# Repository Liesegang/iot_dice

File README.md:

# IoT Dice

サイコロの姿勢・IMUデータをBluetooth Low Energyでブラウザに送り、3D表示するプロジェクトです。

| バージョン | MCU | IMU |
| --- | --- | --- |
| [v1](v1/README.md) | nRF5340 | BNO085 |
| [v2](v2/README.md) | nRF54L15 / ES4L15BA1 | LSM6DSV320X |

```text
v1/
  firmware/  nRF5340用
  hardware/  旧基板データ・回路図
  software/  v1 Webアプリ
v2/
  firmware/  nRF54L15用
  hardware/  Dice 2a基板データ・回路図
  software/  v2 Webアプリ
```

v2では電源投入後にLED2が点滅し、BLE接続中にLED1が点灯します。LSM6DSV320XはLow-gを±16g・120 Hz、High-gを±320g・960 Hz、角速度を±4000dpsに設定しています。High-gはFIFOから取得し、通知間の衝突ピークを保持します。BLE通知は通常約60 Hz、予測／軌跡モードは最大120 Hzです。Web画面では角速度・Low-g・High-g・重力除去後の加速度を4グラフで表示します。

WebアプリはChromeまたはEdgeのHTTPS / localhostで使えます。

```sh
cd v2/software
npm ci
npm run dev -- --host localhost
```

表示されたURLを開き、「サイコロを接続」から`dice`を選んでください。同名デバイスが複数ある場合は対象基板のアドレスで識別します。

GitHub Pagesのワークフローはv1・v2を両方ビルドし、次回デプロイ時にはルートと`/v2/`でv2、`/v1/`でv1を公開します。ファームウェアのビルド・書き込み手順と配線は各バージョンのREADMEを参照してください。

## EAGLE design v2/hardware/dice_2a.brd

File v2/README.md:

# IoT Dice v2 / Dice 2a

KAGA FEI ES4L15BA1（nRF54L15）とLSM6DSV320Xを使う基板です。部品はCADの`PARTS=LSM6DSV320XTR`と実機の`WHO_AM_I=0x73`で識別しています。IC1のdeviceset名はLSM6DSV16XTRのままなので、ドライバー選択には使いません。

## 動作

- LED2（P1.00）：起動直後から500 msごとにON/OFF。IMU初期化が失敗しても点滅します。
- LED1（P1.01）：BLE接続中に点灯、切断時に消灯。
- IMU設定：Low-gは±16g・120 Hz、High-gは±320g・960 Hz、角速度は±4000dps・120 Hz。通常は約60 Hz、軌跡／予測モードは最大120 HzでBLE通知。
- 通常モード：姿勢・角速度・重力除去後の加速度・Low-g／High-g生値と通知間のHigh-gピークを送信。
- 予測モード：最初の衝突前の状態と時刻・投擲番号を送信し、Webで15 mmのサイコロの出目を予測します。実機記録を使う強化学習と検証・テスト評価を追加しました。現時点では必要数の学習用記録が揃っておらず、モデルは未学習・精度未検証です。

SFLPのGame Rotationは磁気センサーを使わないため、ヨーの絶対方位は任意でドリフトすることがあります。

## 配線

| 用途 | nRF54L15 GPIO | モジュールパッド |
| --- | --- | --- |
| LED1 / BLE | P1.01 | 3 |
| LED2 / 起動 | P1.00 | 4 |
| IMU SCK | P2.04 | 9 |
| IMU MOSI | P0.03 | 8 |
| IMU MISO | P0.04 | 7 |
| IMU CS | P2.01 | 10 |
| IMU INT1（未使用） | P1.03 | 5 |

SPIはZephyrのGPIO bitbang、mode 3、設定上限500 kHzです。SCKとデータ線がP2/P0に分かれているため、この配線のまま単一のハードウェアSPIMでは駆動できません。実際の速度はGPIO操作の処理時間にも依存します。FIFOをポーリングします。

P1.00/P1.01をLEDに使うため、低周波クロックは校正ありの内部RCを使用します。電源は安定化された3.3Vを使用してください。

| CON1ピン | 信号 |
| --- | --- |
| 1 | NRST |
| 2 | +3V3 |
| 3 | SWDIO |
| 4 | GND |
| 5 | SWCLK |
| 6 | 未接続 |

基板・回路図は[hardware](hardware/)にあります。`.fbrd` / `.fsch`は元のFusionファイル、`.brd` / `.sch`は取り出したEagle XMLです。

## ビルド・書き込み

nRF Connect SDK 3.4.0の環境で、リポジトリのルートから実行します。

```sh
west build -b nrf54l15dk/nrf54l15/cpuapp -d v2/firmware/build v2/firmware
```

SDKのDKターゲットに`app.overlay`で実基板の配線を適用します。v1用HEXやネットワークコア用ファームウェアはこの基板へ書き込まないでください。

J-Linkとnrfutil deviceを使う場合は対象シリアル番号を確認してから書き込みます。

```sh
nrfutil device list
nrfutil device program \
  --firmware v2/firmware/build/firmware/zephyr/zephyr.hex \
  --serial-number <J-Linkのシリアル番号> \
  --family nrf54l --swd-clock-frequency 1000 \
  --options chip_erase_mode=ERASE_RANGES_TOUCHED_BY_FIRMWARE,verify=VERIFY_READ,reset=RESET_DEFAULT
```

全消去を使わず、HEXに含まれるコード領域だけを書き込みます。RTTログとELFの`app_debug`シンボルで診断できます。SWDで`app_debug`を読む際、MCUを停止させる必要はありません。

## 姿勢デコードとBLE

LSM6DSV320XのSFLP FIFOは姿勢1件を`[0x0000, X, Y]`、`[0x0001, Z, W]`の2レコードで出力します。X/Y/Z/Wは符号付きbinary16です。2件が揃ってから4成分を正規化し、Wの符号も使います。[STの公式FIFO例](https://github.com/STMicroelectronics/STMems_Standard_C_drivers/blob/master/lsm6dsv320x_STdC/examples/lsm6dsv320x_read_fifo.c)を参照してください。

BLE名は`dice`、サービスUUIDは`d1ce0001-1234-5678-abcd-1234567890ab`。通知UUIDは先頭部分が`d1ce0002`、操作UUIDは`d1ce0003`です。

v3の姿勢／ストリーム通知は100バイトです。従来の58バイトの先頭に続き、Low-g生値、High-g最新値、通知間のHigh-g最大ベクトル、有効性・飽和フラグを含みます。通常モードの速度は0です。衝突通知は76バイト、静止通知は44バイトで、High-gの衝突ピークや最大値を記録します。多バイト値はlittle-endianです。詳細は[ble_orient.hpp](firmware/src/ble_orient.hpp)。Webアプリは従来の22/46/58バイト姿勢、50/58バイト衝突、32/36バイト静止も読めます。High-gが届いていない場合は「未受信」と表示します。

## Webアプリとテスト

```sh
cd v2/software
npm ci
npm run dev -- --host localhost
```

配布用ビルドは`npm run build`、型チェックは`npx tsc --noEmit`、BLE・物理モデル・強化学習の回帰テストは`npm test`です。

投擲の記録、6面校正、学習、モデルの保存と再学習については[software/LEARNING.md](software/LEARNING.md)を参照してください。

姿勢FIFOの回帰テストはSDKのSTドライバーをホスト向けにリンクして実行します。左右の符号、180度を超えた回転、2レコードの組み立て、欠損・不正データからの復帰を検証します。

```sh
STMEMSC_DRIVER_DIR=/opt/nordic/ncs/v3.4.0/modules/hal/st/sensor/stmemsc/lsm6dsv320x_STdC/driver \
  sh v2/firmware/tests/run.sh
```

### 推定軌跡の表示

Web画面の「軌跡 ON」で、静止位置を原点にした相対移動を水色の線で表示します。黄色の点が原点です。X/YはIMUの水平軸（向きは任意）、Zは上向きで、移動量はcm表示です。軌跡の取得に面校正や出目予測のONは不要です。静止を検出すると線を消し、次に動き始めると原点を更新します。センサーの微小な揺れや残留速度では線を生成しません。「軌跡を消す」で手動リセットできます。

位置はファームウェアの推定速度をデバイス時刻で積分した値です。外部の位置計測ではなく、IMU誤差の影響を受けます。8秒までの短い動きを対象とし、250msを超える受信の空白では線を消して積分を止め、次の静止を待ちます。軌跡ON中は予測OFFでも速度付きの通知モードを使いますが、学習記録は予測ONの場合だけ保存します。

### 校正表示・IMUグラフ・学習状態

6面の校正は出目判定と3D描画の両方に反映します。表示はサイコロからIMUへの取付回転を掛け、逆の番号配置では面1と6の材質を交換します。静止が300ms以上続いている場合のみ校正でき、不正な面の組み合わせは採用しません。左上に実機の推定上面を表示します。

右上のIMU波形は直近10秒のX/Y/Z角速度（rad/s）、Low-g生加速度（g）、通知間のHigh-gピーク（g）、重力除去後の加速度（m/s²）の4図です。通信が途切れた部分は線をつなぎません。これらはIMU座標系の値です。

学習の実行状況は左上と学習パネルで確認できます。パネルには学習可能な記録数、不足数、校正前・ジャイロ飽和で除外された確認済み記録数、最終実行時刻とモデル採用結果を表示します。正解未確認の記録は学習されません。過去の記録は「未確認の記録に正解を付ける」から、実際の出目を覚えているものだけ確認できます。

### High-gでの衝突取得

Low-gは±16g・120Hz設定で姿勢・静止判定・速度の推定に使います。High-gは±320g・960Hz設定でFIFOへ保存し、通知間の全サンプルから最大ノルムの符号付きベクトルを残します。低速のBLE通知でも、サンプル済みの短い衝突ピークが表示されます。IMUのサンプル間に収まる衝撃まで保証するものではありません。

現在の実機では、MCUの時刻に基づく姿勢取得は約111 Hz、High-g取得は約887 Hzで、High-gは姿勢の約8倍でした。120／960 Hzは設定値で、これらの実測値やBLE通知速度とは異なります。

High-gの重力除去後のピークを初回衝突判定へ反映し、着地結果には投擲中の最大High-gと飽和判定回数を保存します。姿勢予測の入力は従来どおり初回衝突前の姿勢・角速度・速度で、衝突ピークを予測入力に混ぜません。High-gのピーク時刻はFIFOから取り出した際のMCUのuptimeです。厳密なセンサー採取時刻ではありません。

ジャイロは±4000dpsへ拡大し、換算と飽和閾値を合わせています。過去の±2000dps時の飽和記録は元の情報を維持します。高gのゼロ点精度はLow-gより低いため、小さい動きと静止にはLow-gを使います。

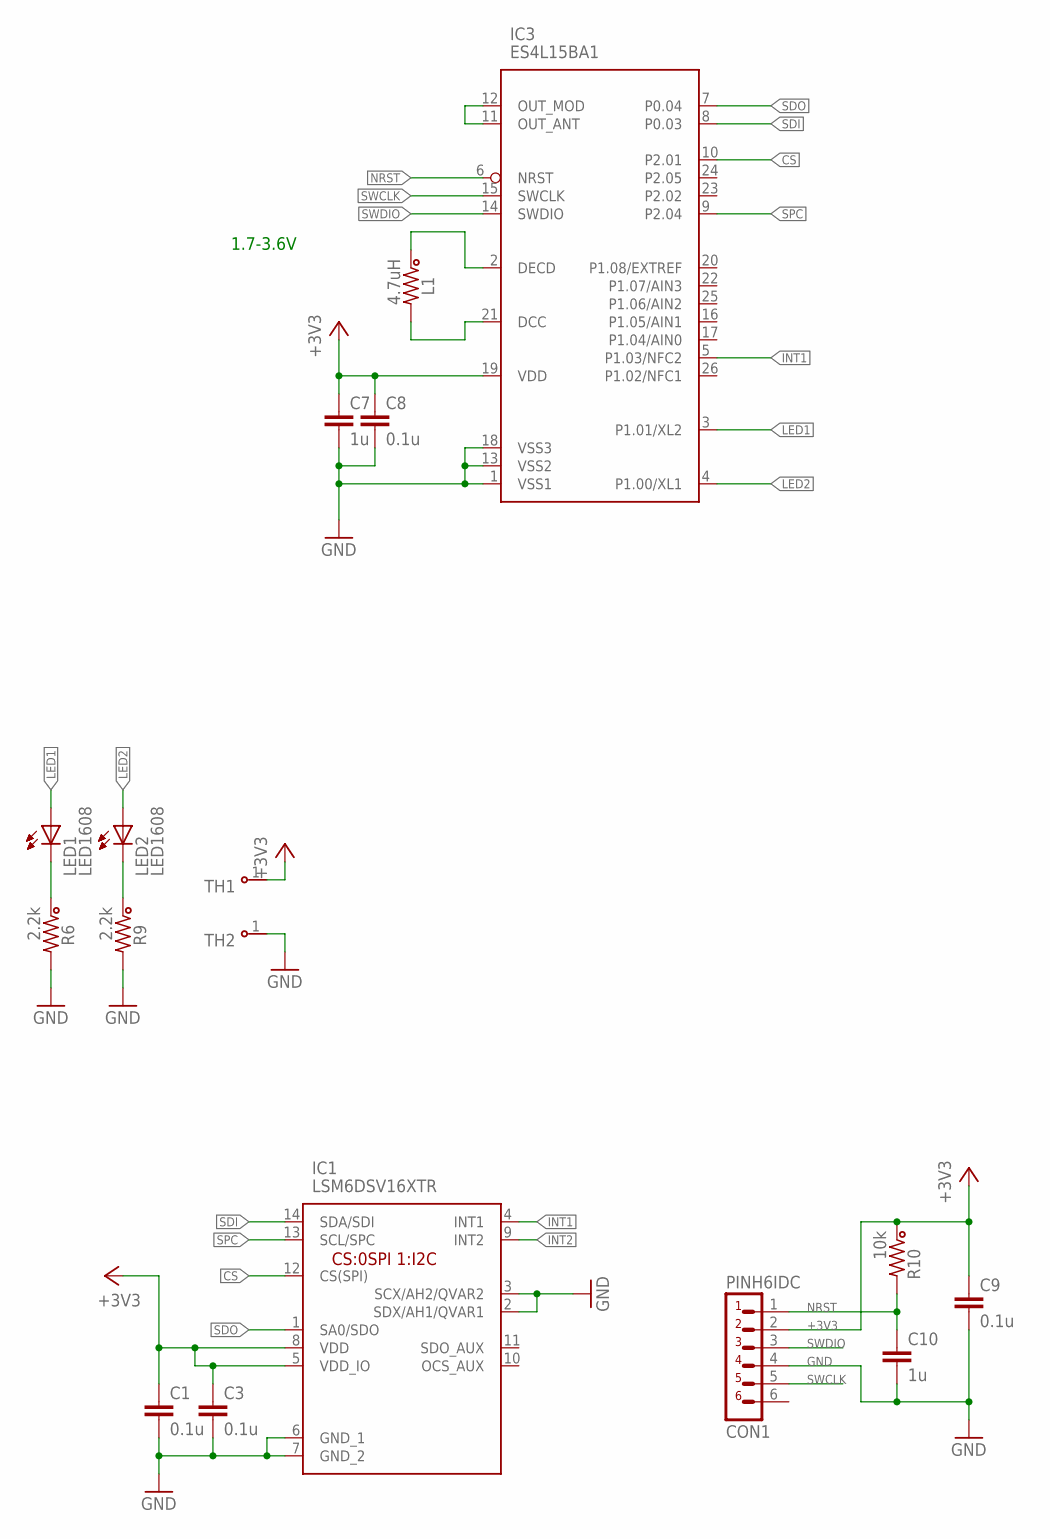
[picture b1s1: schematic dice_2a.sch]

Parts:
C1, C3, C8, C9: 0.1u; 1608A
C7, C10: 1u; 1608A
CON1: PINH6IDC; 1X6IDC_1R27
IC1: LSM6DSV16XTR; LSM6DSV16BXTR; PARTS LSM6DSV320XTR
IC3: ES4L15BA1
L1: 4.7uH; 1608A; PARTS LSQPB160807T4R7M
LED1, LED2: LED1608
R6, R9: 2.2k; 1608A
R10: 10k; 1608A
TH1, TH2: THCHK; 03C

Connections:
+3V3: C1.1, C3.1, C7.1, C8.1, C9.1, CON1.2, IC1.5 (VDD_IO), IC1.8 (VDD), IC3.19 (VDD), R10.1, TH1.1
CS: IC1.12 (CS(SPI)), IC3.10 (P2.01)
GND: C1.2, C3.2, C7.2, C8.2, C9.2, C10.2, CON1.4, IC1.2 (SDX/AH1/QVAR1), IC1.3 (SCX/AH2/QVAR2), IC1.6 (GND_1), IC1.7 (GND_2), IC3.1 (VSS1), IC3.13 (VSS2), IC3.18 (VSS3), R6.2, R9.2, TH2.1
INT1: IC1.4 (INT1), IC3.5 (P1.03/NFC2)
INT2: IC1.9 (INT2)
LED1: IC3.3 (P1.01/XL2), LED1.A
LED2: IC3.4 (P1.00/XL1), LED2.A
unnamed: LED2.K (C), R9.1
unnamed: IC3.11 (OUT_ANT), IC3.12 (OUT_MOD)
unnamed: LED1.K (C), R6.1
unnamed: IC3.2 (DECD), L1.1
unnamed: IC3.21 (DCC), L1.2
NRST: C10.1, CON1.1, IC3.6 (NRST), R10.2
SDI: IC1.14 (SDA/SDI), IC3.8 (P0.03)
SDO: IC1.1 (SA0/SDO), IC3.7 (P0.04)
SPC: IC1.13 (SCL/SPC), IC3.9 (P2.04)
SWCLK: CON1.5, IC3.15 (SWCLK)
SWDIO: CON1.3, IC3.14 (SWDIO)

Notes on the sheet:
1.7-3.6V

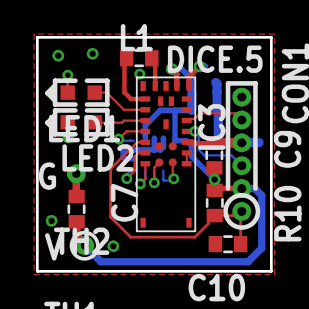
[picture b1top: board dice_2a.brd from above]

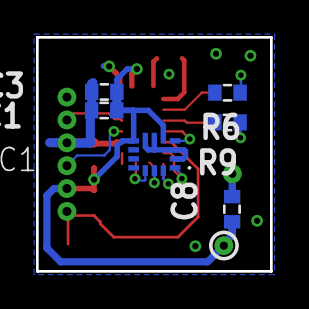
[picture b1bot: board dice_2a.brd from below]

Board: 2 copper layers, 13.0 x 13.0 mm, 17 parts (6 on the bottom side), 17 nets.

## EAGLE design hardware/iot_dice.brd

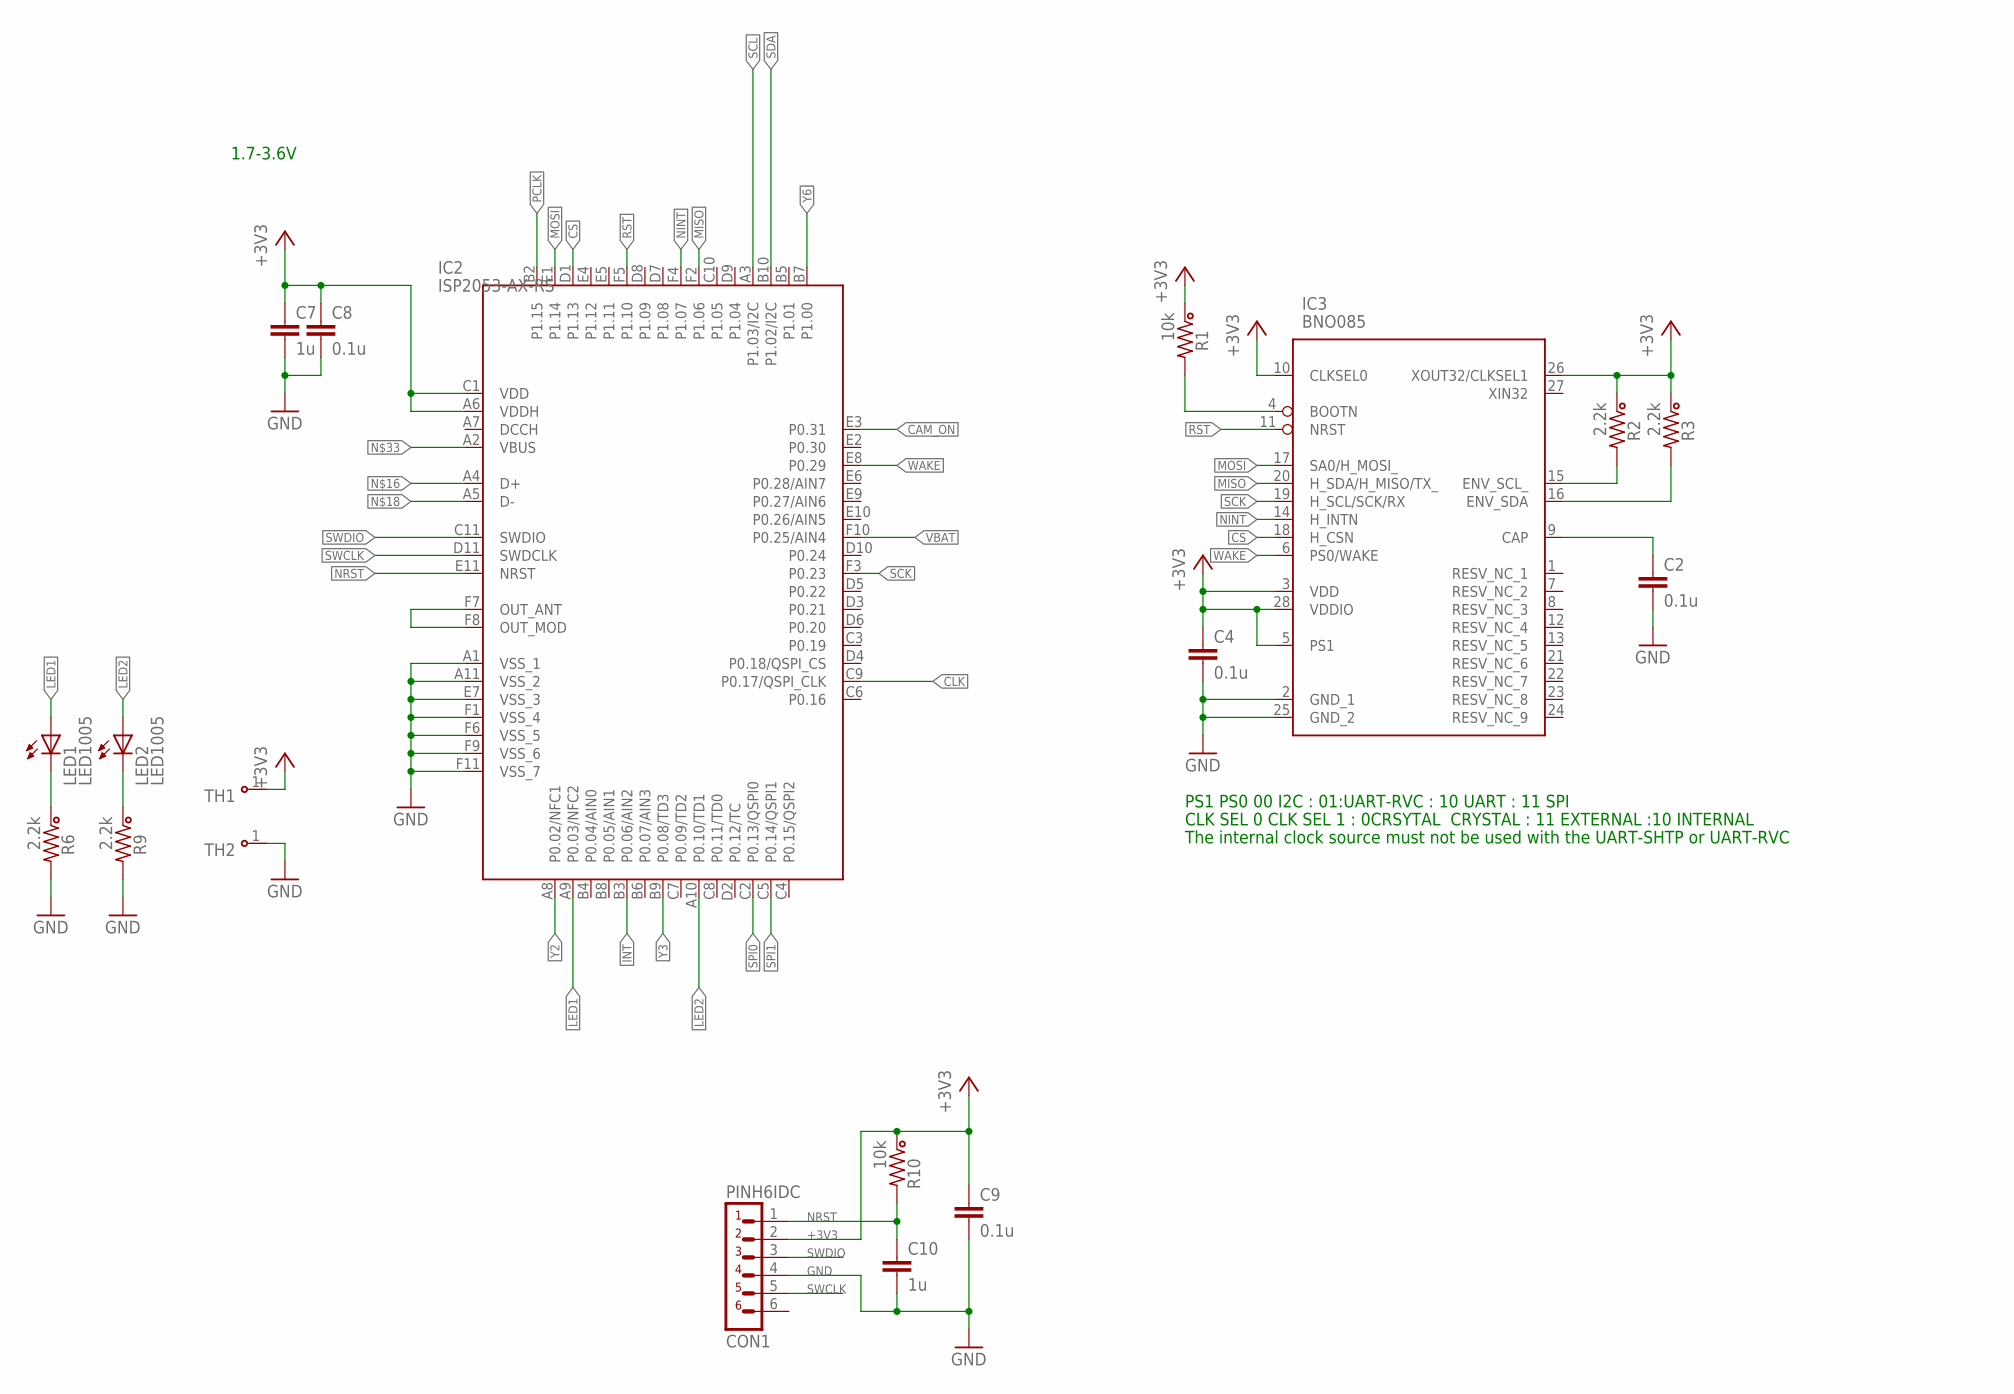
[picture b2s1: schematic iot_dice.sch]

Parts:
C2, C4, C8, C9: 0.1u; 1005K
C7, C10: 1u; 1005K
CON1: PINH6IDC; 1X6IDC_1R27
IC2: ISP2053-AX-RS; ISP2053AXRS
IC3: BNO085
LED1, LED2: LED1005; 1005K-LED
R1, R10: 10k; 1005K
R2, R3, R6, R9: 2.2k; 1005K
TH1, TH2: THCHK; 03C

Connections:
+3V3: C4.1, C7.1, C8.1, C9.1, CON1.2, IC2.A6 (VDDH), IC2.C1 (VDD), IC3.3 (VDD), IC3.5 (PS1), IC3.10 (CLKSEL0), IC3.26 (XOUT32/CLKSEL1), IC3.28 (VDDIO), R1.1, R2.1, R3.1, R10.1, TH1.1
CAM_ON: IC2.E3 (P0.31)
CLK: IC2.C9 (P0.17/QSPI_CLK)
CS: IC2.D1 (P1.13), IC3.18 (H_CSN)
GND: C2.2, C4.2, C7.2, C8.2, C9.2, C10.2, CON1.4, IC2.A1 (VSS_1), IC2.A11 (VSS_2), IC2.E7 (VSS_3), IC2.F1 (VSS_4), IC2.F6 (VSS_5), IC2.F9 (VSS_6), IC2.F11 (VSS_7), IC3.2 (GND_1), IC3.25 (GND_2), R6.2, R9.2, TH2.1
INT: IC2.B3 (P0.06/AIN2)
LED1: IC2.A9 (P0.03/NFC2), LED1.A
LED2: IC2.A10 (P0.10/TD1), LED2.A
MISO: IC2.F2 (P1.06), IC3.20 (H_SDA/H_MISO/TX_)
MOSI: IC2.E1 (P1.14), IC3.17 (SA0/H_MOSI_)
unnamed: LED2.K (C), R9.1
unnamed: IC2.F7 (OUT_ANT), IC2.F8 (OUT_MOD)
unnamed: LED1.K (C), R6.1
unnamed: C2.1, IC3.9 (CAP)
unnamed: IC3.4 (BOOTN), R1.2
unnamed: IC3.15 (ENV_SCL_), R2.2
unnamed: IC3.16 (ENV_SDA), R3.2
NINT: IC2.F4 (P1.07), IC3.14 (H_INTN)
NRST: C10.1, CON1.1, IC2.E11 (NRST), R10.2
PCLK: IC2.B2 (P1.15)
RST: IC2.F5 (P1.10), IC3.11 (NRST)
SCK: IC2.F3 (P0.23), IC3.19 (H_SCL/SCK/RX)
SCL: IC2.A3 (P1.03/I2C)
SDA: IC2.B10 (P1.02/I2C)
SPI0: IC2.C2 (P0.13/QSPI0)
SPI1: IC2.C5 (P0.14/QSPI1)
SWCLK: CON1.5, IC2.D11 (SWDCLK)
SWDIO: CON1.3, IC2.C11 (SWDIO)
VBAT: IC2.F10 (P0.25/AIN4)
WAKE: IC2.E8 (P0.29), IC3.6 (PS0/WAKE)
Y2: IC2.A8 (P0.02/NFC1)
Y3: IC2.B9 (P0.08/TD3)
Y6: IC2.B7 (P1.00)

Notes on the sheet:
1.7-3.6V
PS1 PS0 00 I2C : 01:UART-RVC : 10 UART : 11 SPI
CLK SEL 0 CLK SEL 1 : 0CRSYTAL CRYSTAL : 11 EXTERNAL :10 INTERNAL
The internal clock source must not be used with the UART-SHTP or UART-RVC

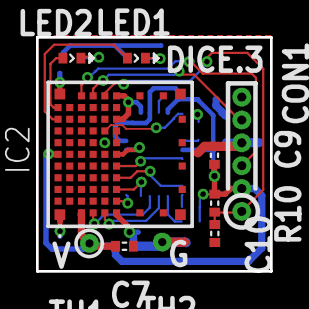
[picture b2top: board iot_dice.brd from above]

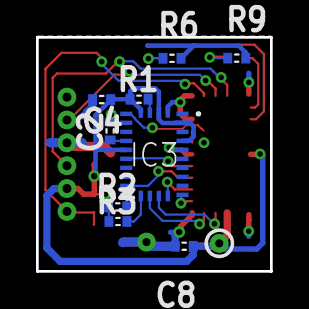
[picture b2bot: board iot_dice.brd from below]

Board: 2 copper layers, 13.0 x 13.0 mm, 19 parts (9 on the bottom side), 21 nets.

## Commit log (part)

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2026-06-09 Initial commit for dice-test2
2026-06-09 Refactor to C++: BNO085 driver class with GPIO interrupt, module split
